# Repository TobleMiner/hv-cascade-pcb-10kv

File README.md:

High Voltage Cascade
====================

Simple PCB layout for high voltage cascades. Input can be up to 10 kV AC

PCB top view

PCB bottom view

PCB measurements

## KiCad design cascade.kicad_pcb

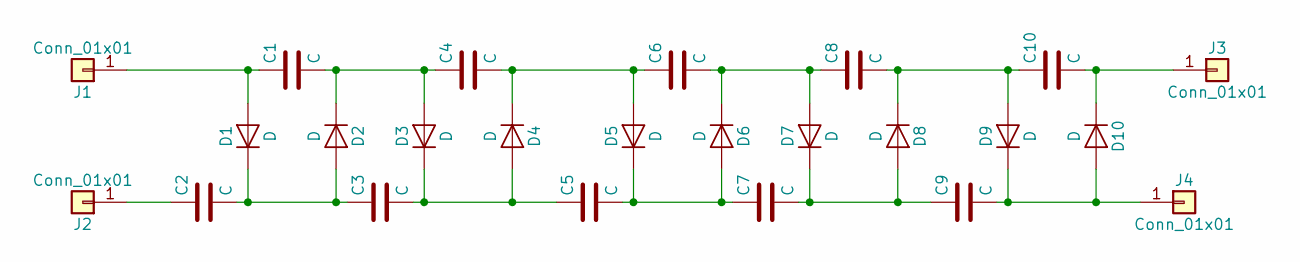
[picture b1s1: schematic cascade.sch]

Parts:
C1, C2, C3, C4, C5, C6, C7, C8, C9, C10: C; cap_20kv_10nf
D1, D2, D3, D4, D5, D6, D7, D8, D9, D10: D; diode_2CL2FM
J1, J2, J3, J4: Conn_01x01; hv_pad

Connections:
unnamed: C1.1, D1.2 (A), J1.1
unnamed: C1.2, C4.1, D2.1 (K), D3.2 (A)
unnamed: C2.1, J2.1
unnamed: C2.2, C3.1, D1.1 (K), D2.2 (A)
unnamed: C3.2, C5.1, D3.1 (K), D4.2 (A)
unnamed: C4.2, C6.1, D4.1 (K), D5.2 (A)
unnamed: C5.2, C7.1, D5.1 (K), D6.2 (A)
unnamed: C6.2, C8.1, D6.1 (K), D7.2 (A)
unnamed: C7.2, C9.1, D7.1 (K), D8.2 (A)
unnamed: C9.2, D9.1 (K), D10.2 (A), J4.1
unnamed: C8.2, C10.1, D8.1 (K), D9.2 (A)
unnamed: C10.2, D10.1 (K), J3.1

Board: 2 copper layers, 24 parts (0 on the bottom side), 12 nets, no tracks yet.

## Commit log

2018-06-09 Add README
2018-06-09 Add PCB measurements
2018-06-09 Move to new high density design
2018-06-09 Update pcb images
